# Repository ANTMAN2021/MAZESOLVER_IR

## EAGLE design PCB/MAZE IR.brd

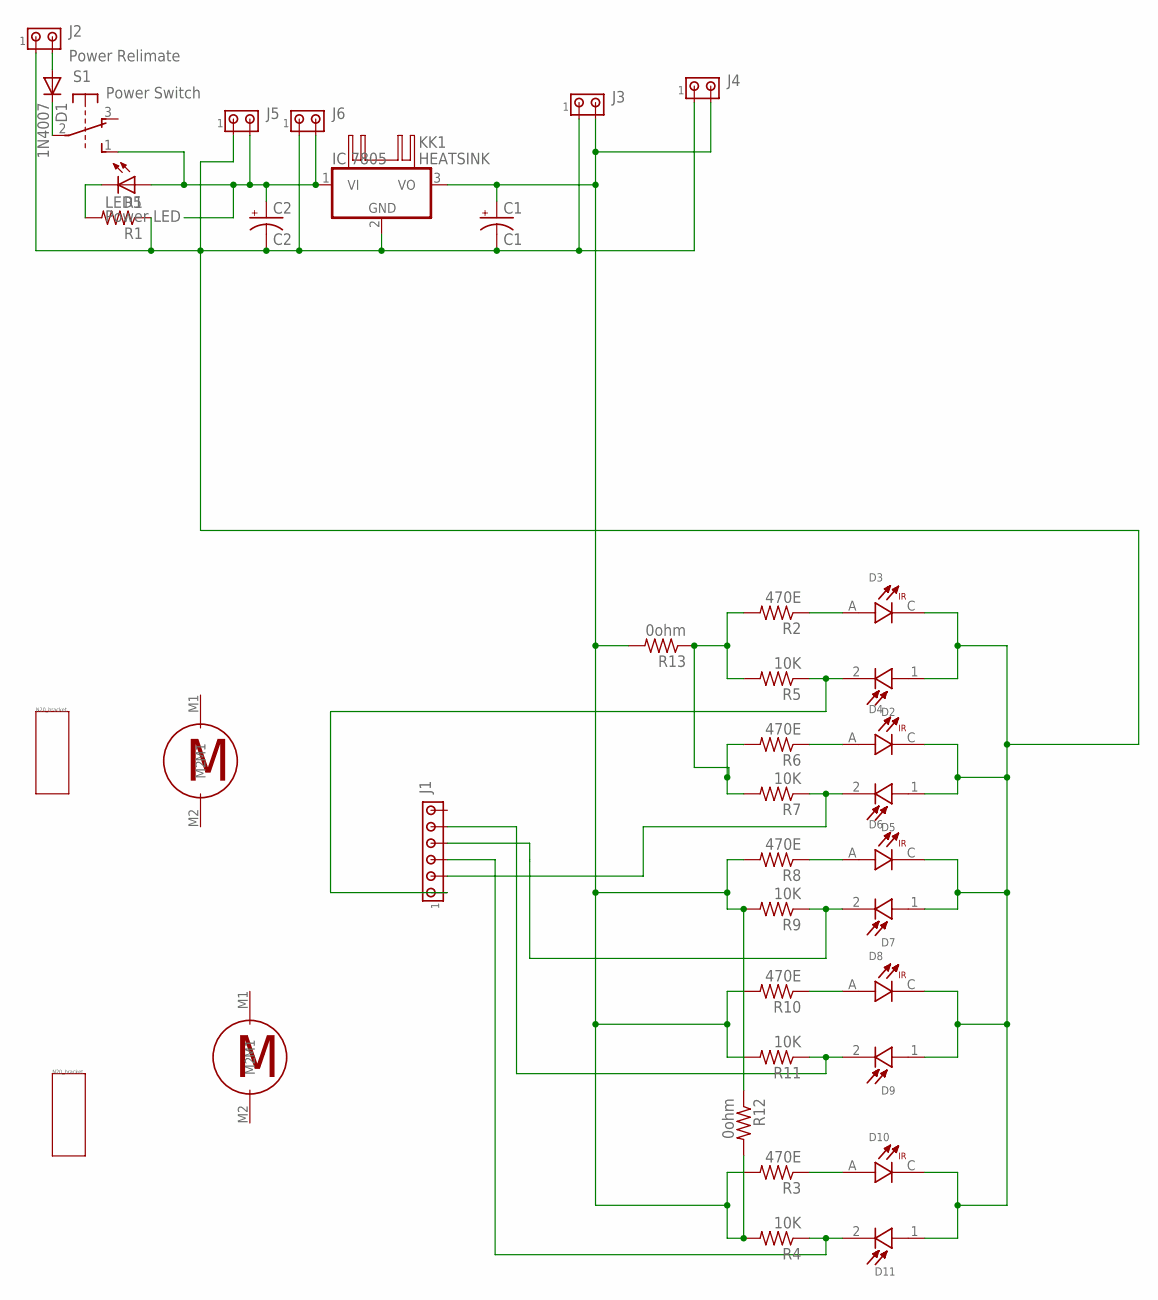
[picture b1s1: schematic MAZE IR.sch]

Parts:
C1: C1; CPOL-RADIAL-5MM-10MM
C2: C2; E3,5-8
D1: 1N4007; DO41-10
D2, D5, D7, D9, D11: SFH_213_FA; XDCR_SFH_213_FA
D3, D4, D6, D8, D10: TSHG8200; LEDRD254W55D595H900
IC3: IC 7805; TO220V
J1: Line Tracer Relimate; 10X06MTA
J2, J3, J4, J5, J6: Power Relimate; 10X02MTA
KK1: HEATSINK
LED5: Power LED; LED3MM
R1: R1; 0204/7
R2, R3, R6, R8, R10: 470E; 0204/7
R4, R5, R7, R9, R11: 10K; 0204/7
R12, R13: 0ohm; 0204/7
S1: Power Switch; 9077-2
U$1, U$2: MOTOR_N20
U$4, U$5: N20_BRACKET; BRACKER

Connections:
5V1: C1.+, IC3.3 (VO), J3.2, J4.2, R3.2, R4.2, R8.2, R9.2, R10.2, R11.2, R12.1, R12.2, R13.2
12V: C2.+, IC3.1 (VI), J5.2, J6.2, LED5.A, S1.1 (S)
GND1: C1.-, C2.-, D2.1 (A), D3.C, D4.C, D5.1 (A), D6.C, D7.1 (A), D8.C, D9.1 (A), D10.C, D11.1 (A), IC3.2 (GND), J2.1, J3.1, J4.1, J5.1, J6.1, R1.1
unnamed: D10.A, R3.1
unnamed: D1.A, J2.2
unnamed: D11.2 (C), J1.4 (3), R4.1
unnamed: R2.2, R5.2, R6.2, R7.2, R13.1
unnamed: LED5.K (C), R1.2
unnamed: D3.A, R2.1
unnamed: D1.C, S1.2
unnamed: D2.2 (C), J1.6 (1), R5.1
unnamed: D9.2 (C), J1.2 (5), R11.1
unnamed: D4.A, R6.1
unnamed: D5.2 (C), J1.5 (2), R7.1
unnamed: D6.A, D8.A, R8.1, R10.1
unnamed: D7.2 (C), J1.3 (4), R9.1

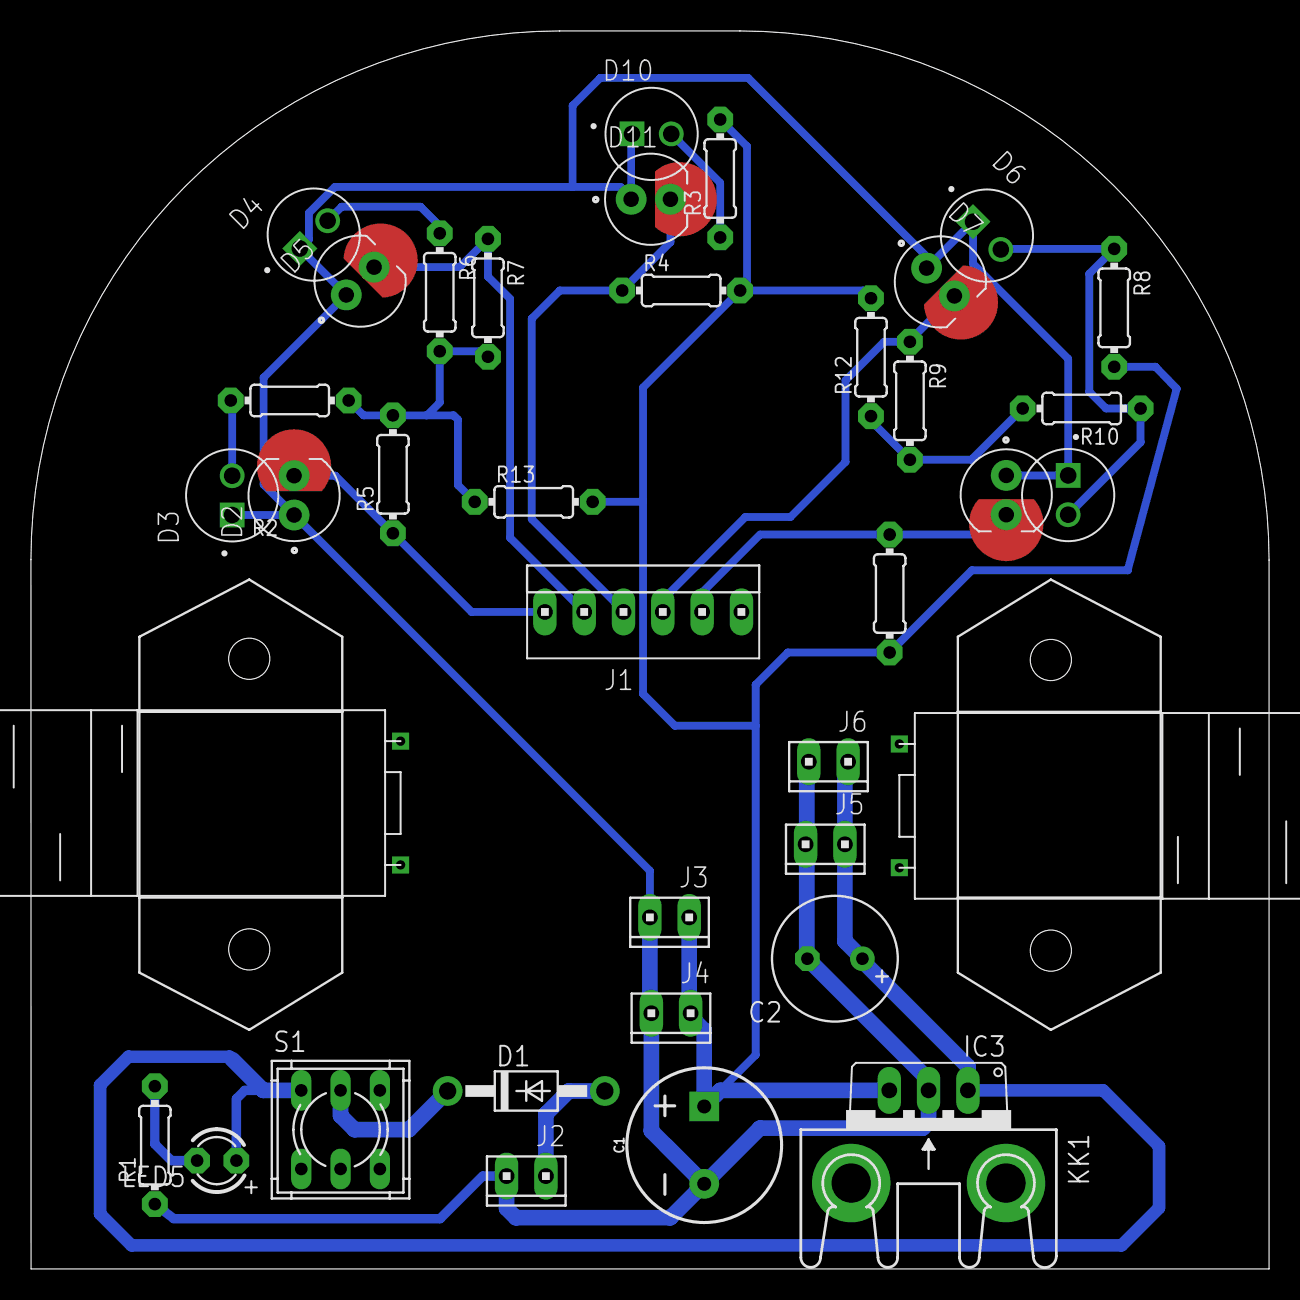
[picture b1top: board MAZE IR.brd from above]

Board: 2 copper layers, 80.0 x 80.0 mm, 40 parts (0 on the bottom side), 16 nets.

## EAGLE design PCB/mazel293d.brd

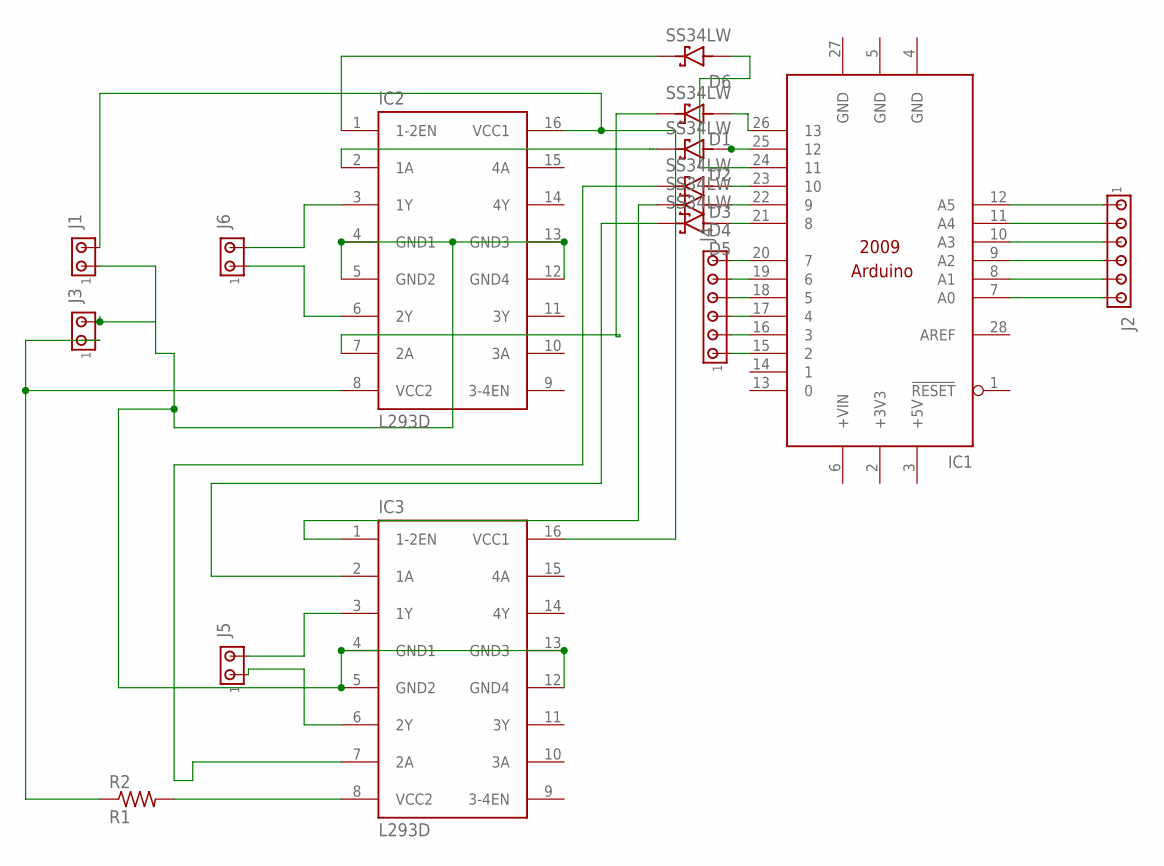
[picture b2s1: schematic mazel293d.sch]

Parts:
D1, D2, D3, D4, D5, D6: SS34LW; SODFL3718X102N
IC1: ARDUINO2009_10; ARDUINO2009
IC2, IC3: L293D; DIL16
J1, J3, J5, J6: MTA02-100; 10X02MTA
J2, J4: Line Tracer Relimate; 10X06MTA
R2: R1; 0204/7

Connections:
+3V3: IC1.2 (+3V3)
+5V: IC1.3 (+5V)
GND: IC1.4 (GND), IC1.5 (GND), IC1.27 (GND)
unnamed: IC3.8 (VCC2), R2.2
unnamed: IC1.12 (A5), J2.6 (1)
unnamed: IC3.3 (1Y), J5.2
unnamed: IC3.6 (2Y), J5.1
unnamed: D1.A, IC1.26 (13)
unnamed: IC2.3 (1Y), J6.2
unnamed: IC1.20 (7), J4.1 (6)
unnamed: IC1.19 (6), J4.2 (5)
unnamed: IC2.6 (2Y), J6.1
unnamed: D6.C (K), IC2.1 (1-2EN)
unnamed: IC1.18 (5), J4.3 (4)
unnamed: IC2.4 (GND1), IC2.5 (GND2), IC2.12 (GND4), IC2.13 (GND3), IC3.4 (GND1), IC3.5 (GND2), IC3.12 (GND4), IC3.13 (GND3), J1.1, J3.2
unnamed: D2.C (K), IC2.2 (1A)
unnamed: D2.A, IC1.25 (12)
unnamed: IC1.17 (4), J4.4 (3)
unnamed: IC1.16 (3), J4.5 (2)
unnamed: IC1.15 (2), J4.6 (1)
unnamed: IC1.11 (A4), J2.5 (2)
unnamed: IC1.10 (A3), J2.4 (3)
unnamed: IC1.9 (A2), J2.3 (4)
unnamed: IC1.8 (A1), J2.2 (5)
unnamed: IC1.7 (A0), J2.1 (6)
unnamed: D1.C (K), IC2.7 (2A)
unnamed: D3.C (K), IC3.7 (2A)
unnamed: D5.C (K), IC3.2 (1A)
unnamed: D4.C (K), IC3.1 (1-2EN)
unnamed: D3.A, IC1.23 (10)
unnamed: D4.A, IC1.22 (9)
unnamed: D5.A, IC1.21 (8)
unnamed: IC2.16 (VCC1), IC3.16 (VCC1), J1.2
unnamed: D6.A, IC1.24 (11)
unnamed: IC2.8 (VCC2), J3.1, R2.1

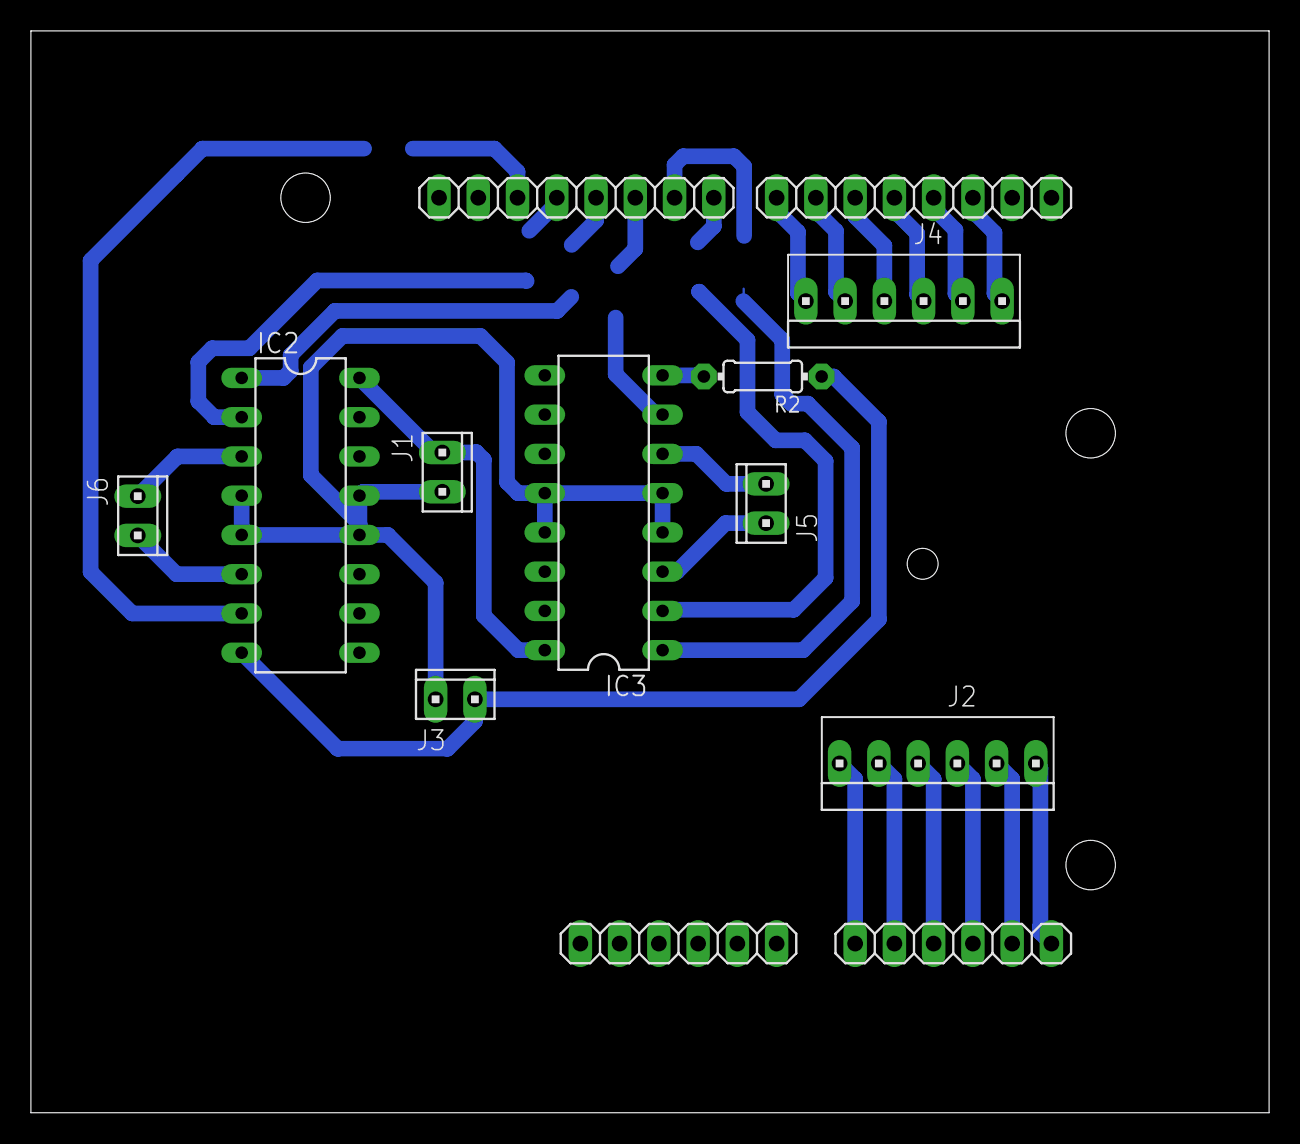
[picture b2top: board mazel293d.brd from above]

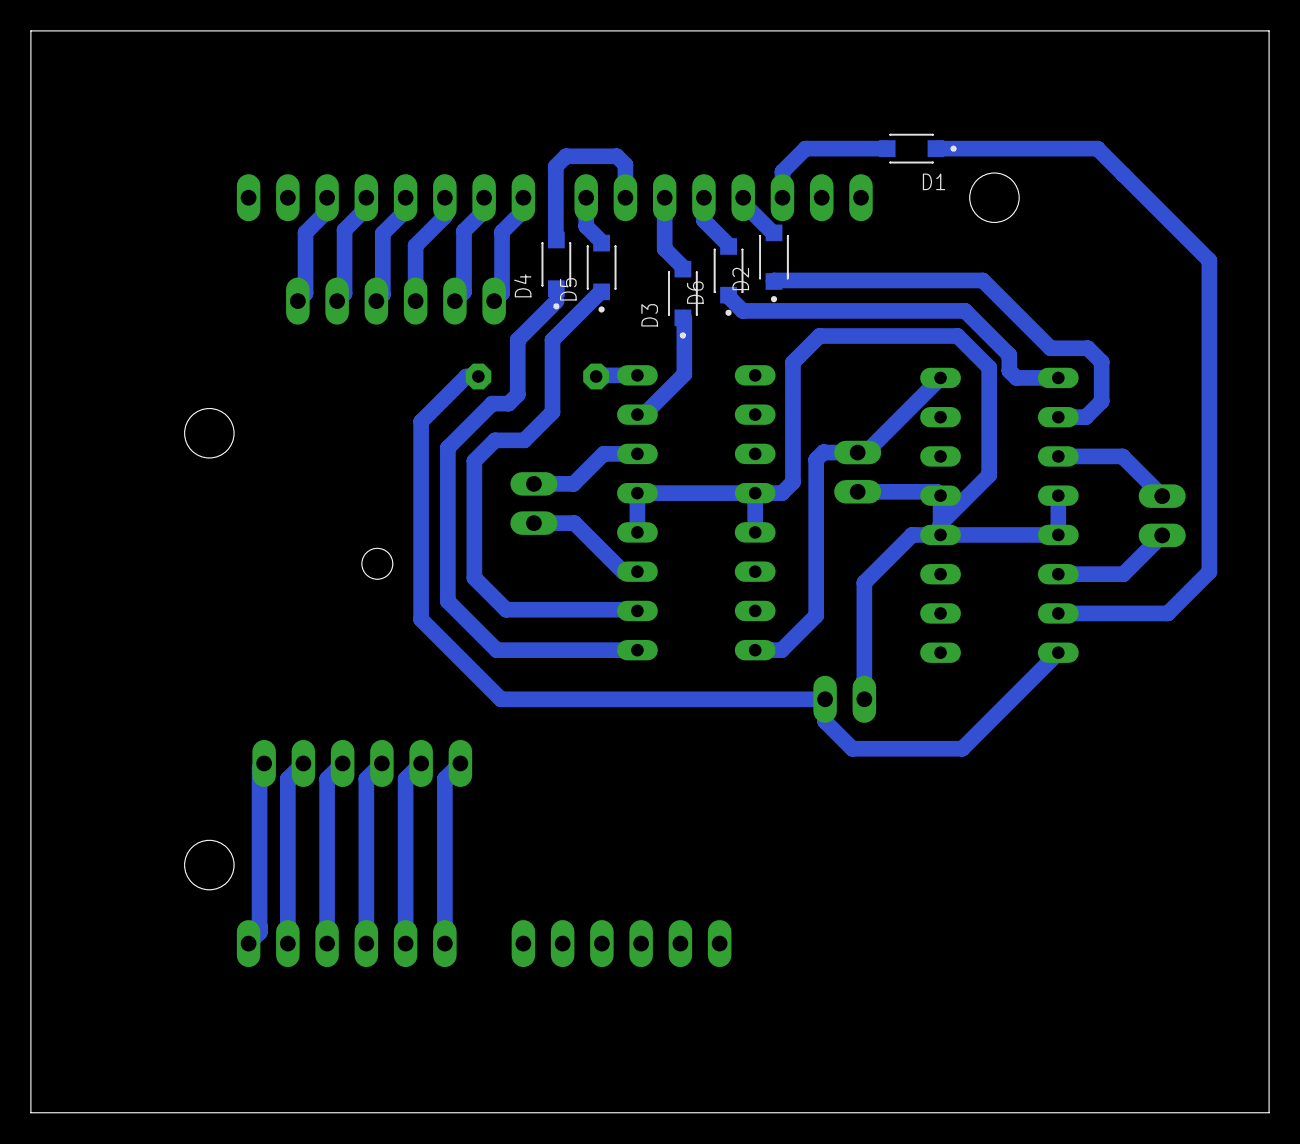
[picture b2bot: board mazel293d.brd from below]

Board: 2 copper layers, 80.1 x 70.0 mm, 16 parts (6 on the bottom side), 33 nets.

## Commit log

2024-08-04 Create pcb

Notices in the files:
parts and their libraries:
SparkFun-Capacitors: Licensing: Creative Commons ShareAlike 4.0 International - https://creativecommons.org/licenses/by-sa/4.0
heatsink: Copyright (C) 2004, Bob Starr (bobstarr@mindspring.com)
